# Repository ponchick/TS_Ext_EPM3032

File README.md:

# TS_Ext_EPM3032
EPM3032-based TurboSound extension card for ZXBUS

[CPLD Firmware](https://github.com/MikhaelKaa/Double_ym2149_epm3032)

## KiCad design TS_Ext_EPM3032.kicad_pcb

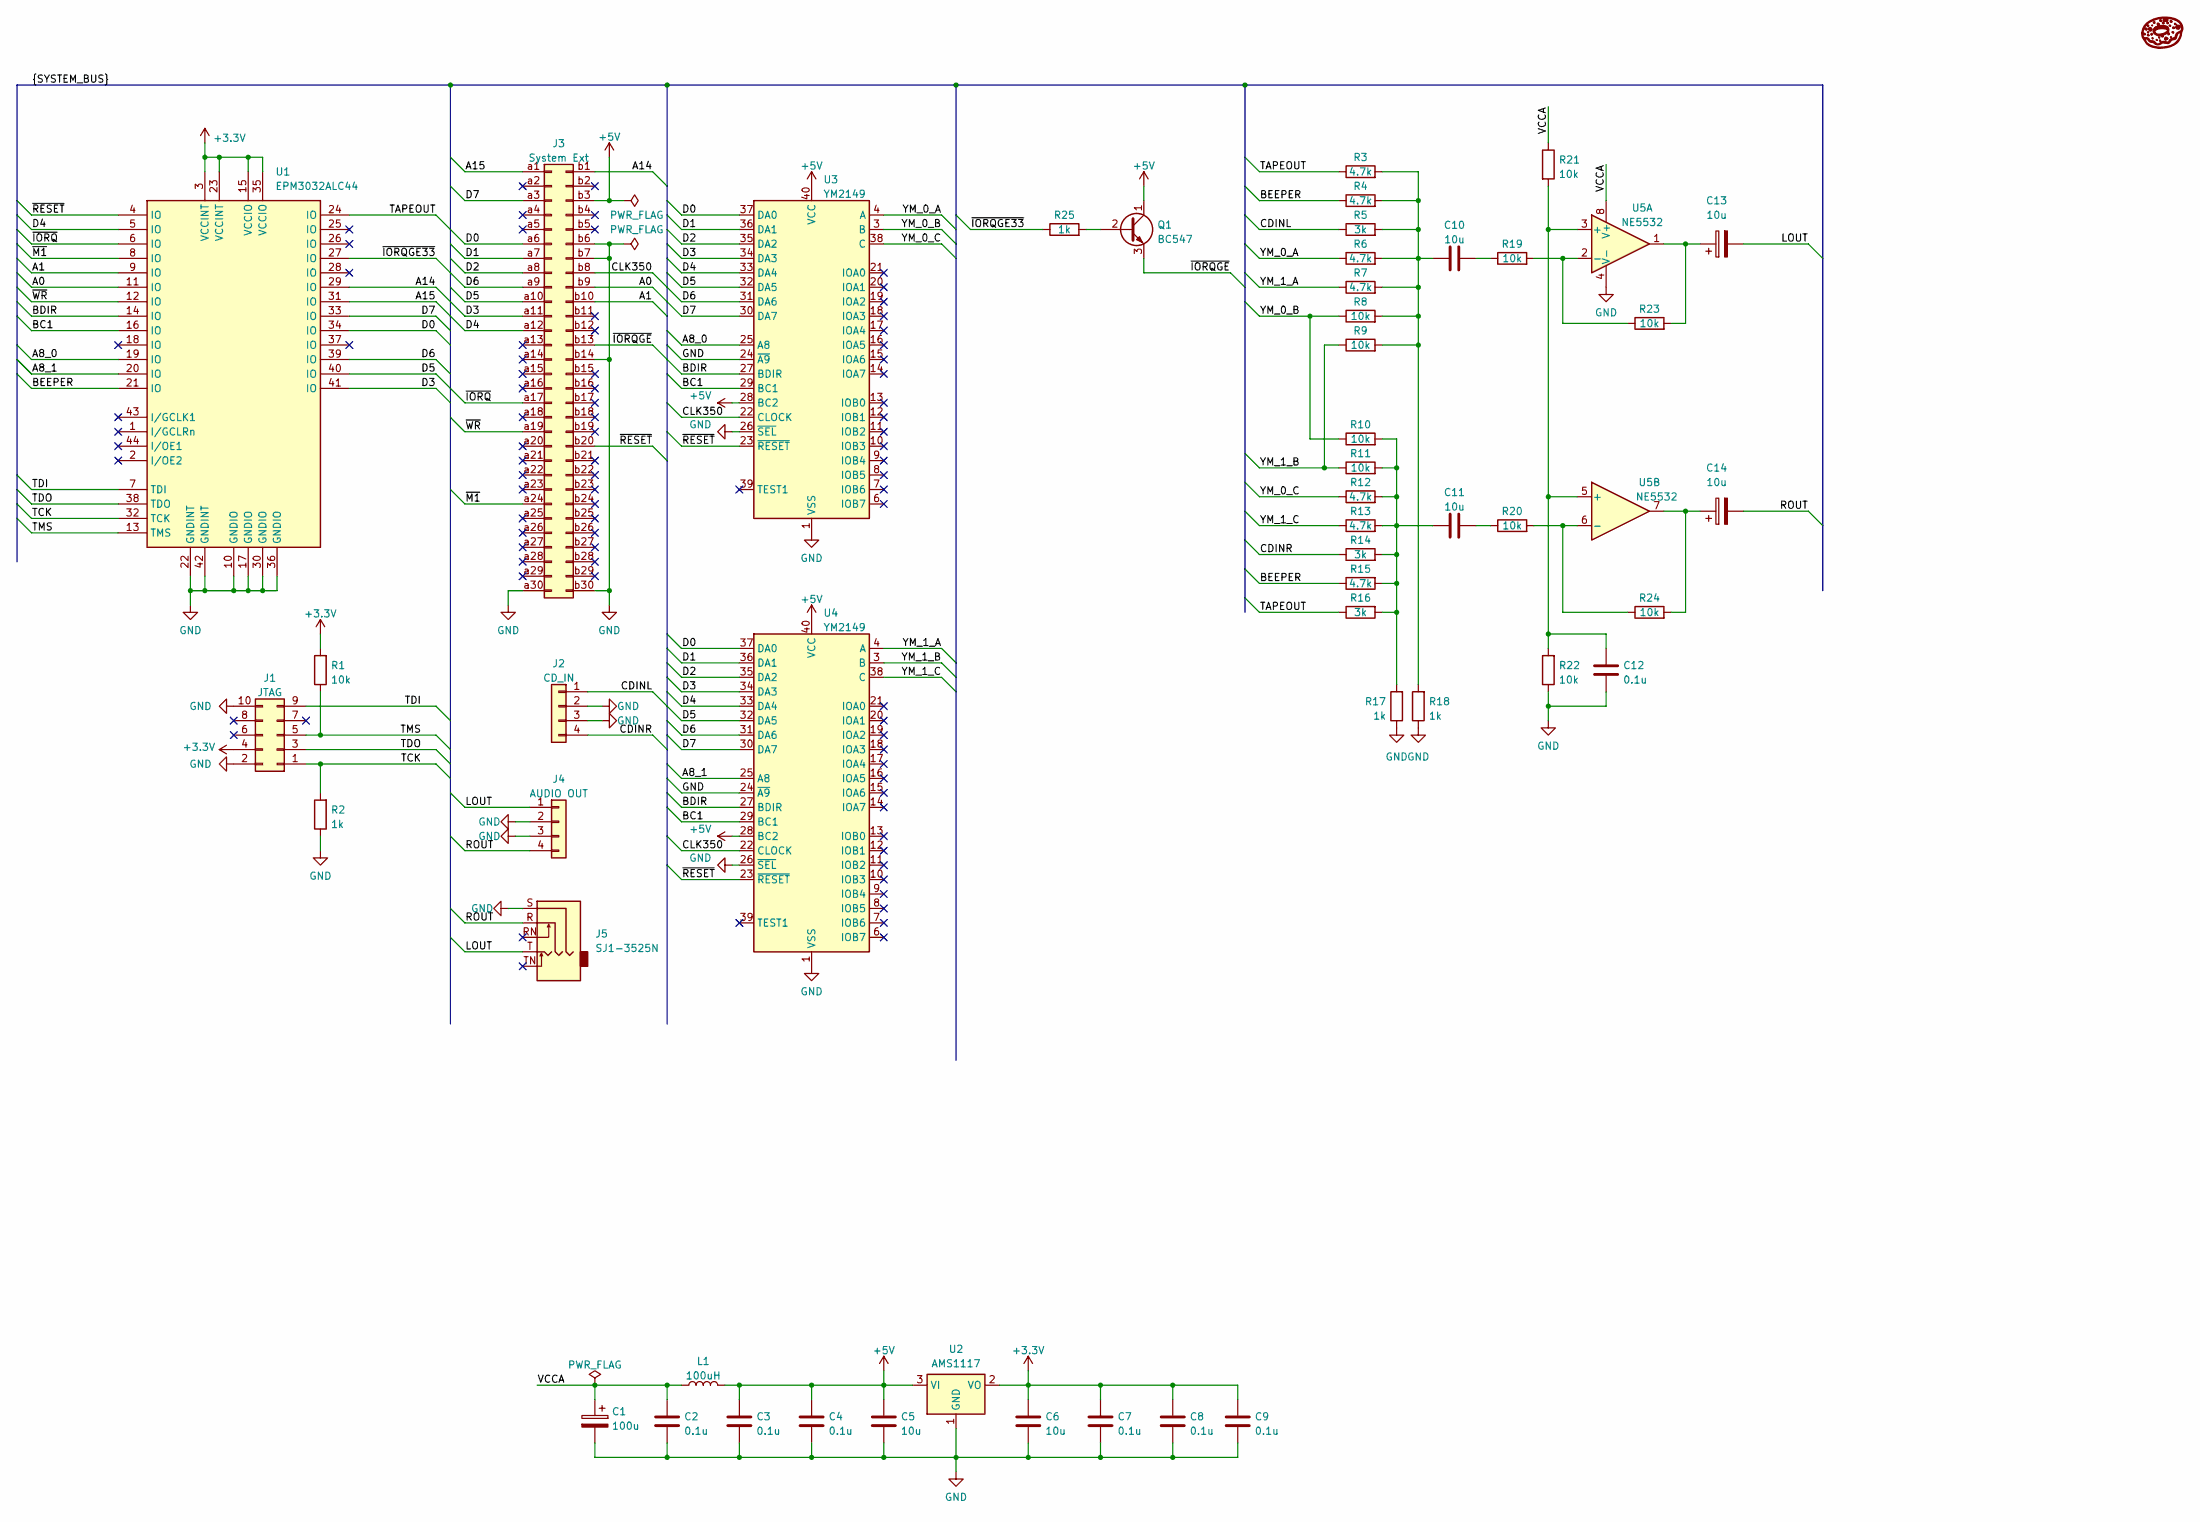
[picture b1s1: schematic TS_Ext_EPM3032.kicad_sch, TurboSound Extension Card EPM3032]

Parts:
C1: 100u; CP_Radial_D5.0mm_P2.50mm
C2, C3, C4, C7, C8, C9, C12: 0.1u; C_Disc_D4.3mm_W1.9mm_P5.00mm
C5, C6: 10u; C_Disc_D4.3mm_W1.9mm_P5.00mm
C10, C11: 10u; C_Rect_L7.0mm_W2.0mm_P5.00mm
C13, C14: 10u; CP_Radial_D5.0mm_P2.50mm
J1: JTAG; IDC-Header_2x05_P2.54mm_Vertical
J2: CD_IN; PinHeader_1x04_P2.54mm_Vertical
J3: System Ext; EDGE SLOT
J4: AUDIO OUT; PinHeader_1x04_P2.54mm_Vertical
J5: SJ1-3525N; Jack_3.5mm_CUI_SJ1-3525N_Horizontal
L1: 100uH; L_Radial_D8.7mm_P5.00mm_Fastron_07HCP
LOGO1: LOGO; ponchick
Q1: BC547; TO-92_Inline
R1, R8, R9, R10, R11, R19, R20, R21, R22, R23, R24: 10k; R_Axial_DIN0204_L3.6mm_D1.6mm_P7.62mm_Horizontal
R2, R17, R18, R25: 1k; R_Axial_DIN0204_L3.6mm_D1.6mm_P7.62mm_Horizontal
R3, R4, R6, R7, R12, R13, R15: 4.7k; R_Axial_DIN0204_L3.6mm_D1.6mm_P7.62mm_Horizontal
R5, R14, R16: 3k; R_Axial_DIN0204_L3.6mm_D1.6mm_P7.62mm_Horizontal
U1: EPM3032ALC44; PLCC-44_THT-Socket
U2: AMS1117; SOT-223-3_TabPin2
U3, U4: YM2149; DIP-40_W15.24mm_Socket
U5: NE5532; DIP-8_W7.62mm_Socket

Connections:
+3.3V: C6.1, C7.1, C8.1, C9.1, J1.4, R1.2, U1.3 (VCCINT), U1.15 (VCCIO), U1.23 (VCCINT), U1.35 (VCCIO), U2.2 (VO)
+5V: C3.1, C4.1, C5.1, J3.b3, L1.2, Q1.1 (C), U2.3 (VI), U3.28 (BC2), U3.40 (VCC), U4.28 (BC2), U4.40 (VCC)
/A0: J3.b9, U1.11 (IO)
/A1: J3.b10, U1.9 (IO)
/A8_0: U1.19 (IO), U3.25 (A8)
/A8_1: U1.20 (IO), U4.25 (A8)
/A14: J3.b1, U1.29 (IO)
/A15: J3.a1, U1.31 (IO)
/BC1: U1.16 (IO), U3.29 (BC1), U4.29 (BC1)
/BDIR: U1.14 (IO), U3.27 (BDIR), U4.27 (BDIR)
/BEEPER: R4.1, R15.1, U1.21 (IO)
/CDINL: J2.1, R5.1
/CDINR: J2.4, R14.1
/CLK350: J3.b8, U3.22 (CLOCK), U4.22 (CLOCK)
/D0: J3.a6, U1.34 (IO), U3.37 (DA0), U4.37 (DA0)
/D1: J3.a7, U3.36 (DA1), U4.36 (DA1)
/D2: J3.a8, U3.35 (DA2), U4.35 (DA2)
/D3: J3.a11, U1.41 (IO), U3.34 (DA3), U4.34 (DA3)
/D4: J3.a12, U1.5 (IO), U3.33 (DA4), U4.33 (DA4)
/D5: J3.a10, U1.40 (IO), U3.32 (DA5), U4.32 (DA5)
/D6: J3.a9, U1.39 (IO), U3.31 (DA6), U4.31 (DA6)
/D7: J3.a3, U1.33 (IO), U3.30 (DA7), U4.30 (DA7)
/LOUT: C13.2, J4.1, J5.T
/ROUT: C14.2, J4.4, J5.R
/TAPEOUT: R3.1, R16.1, U1.24 (IO)
/TCK: J1.1, R2.2, U1.32 (TCK)
/TDI: J1.9, U1.7 (TDI)
/TDO: J1.3, U1.38 (TDO)
/TMS: J1.5, R1.1, U1.13 (TMS)
/VCCA: C1.1, C2.1, L1.1, R21.1, U5.8 (V+)
/YM_0_A: R6.1, U3.4 (A)
/YM_0_B: R8.1, R10.1, U3.3 (B)
/YM_0_C: R12.1, U3.38 (C)
/YM_1_A: R7.1, U4.4 (A)
/YM_1_B: R9.1, R11.1, U4.3 (B)
/YM_1_C: R13.1, U4.38 (C)
/~IORQGE33: R25.1, U1.27 (IO)
/~IORQGE: J3.b13, Q1.3 (E)
/~IORQ: J3.a17, U1.6 (IO)
/~M1: J3.a24, U1.8 (IO)
/~RESET: J3.b20, U1.4 (IO), U3.23 (~RESET), U4.23 (~RESET)
/~WR: J3.a19, U1.12 (IO)
GND: C1.2, C2.2, C3.2, C4.2, C5.2, C6.2, C7.2, C8.2, C9.2, C12.2, J1.2, J1.10, J2.2, J2.3, J3.a30, J3.b6, J3.b7, J3.b14, J3.b30, J4.2, J4.3, J5.S, R2.1, R17.1, R18.1, R22.1, U1.10 (GNDIO), U1.17 (GNDIO), U1.22 (GNDINT), U1.30 (GNDIO), U1.36 (GNDIO), U1.42 (GNDINT), U2.1 (GND), U3.1 (VSS), U3.24 (~A9), U3.26 (~SEL), U4.1 (VSS), U4.24 (~A9), U4.26 (~SEL), U5.4 (V-)
unnamed: C10.1, R3.2, R4.2, R5.2, R6.2, R7.2, R8.2, R9.2, R18.2
unnamed: C10.2, R19.1
unnamed: C11.1, R20.1
unnamed: C11.2, R10.2, R11.2, R12.2, R13.2, R14.2, R15.2, R16.2, R17.2
unnamed: C13.1, R23.2, U5.1
unnamed: C14.1, R24.2, U5.7
unnamed: Q1.2 (B), R25.2
unnamed: C12.1, R21.2, R22.2, U5.3 (+), U5.5 (+)
unnamed: R19.2, R23.1, U5.2 (-)
unnamed: R20.2, R24.1, U5.6 (-)

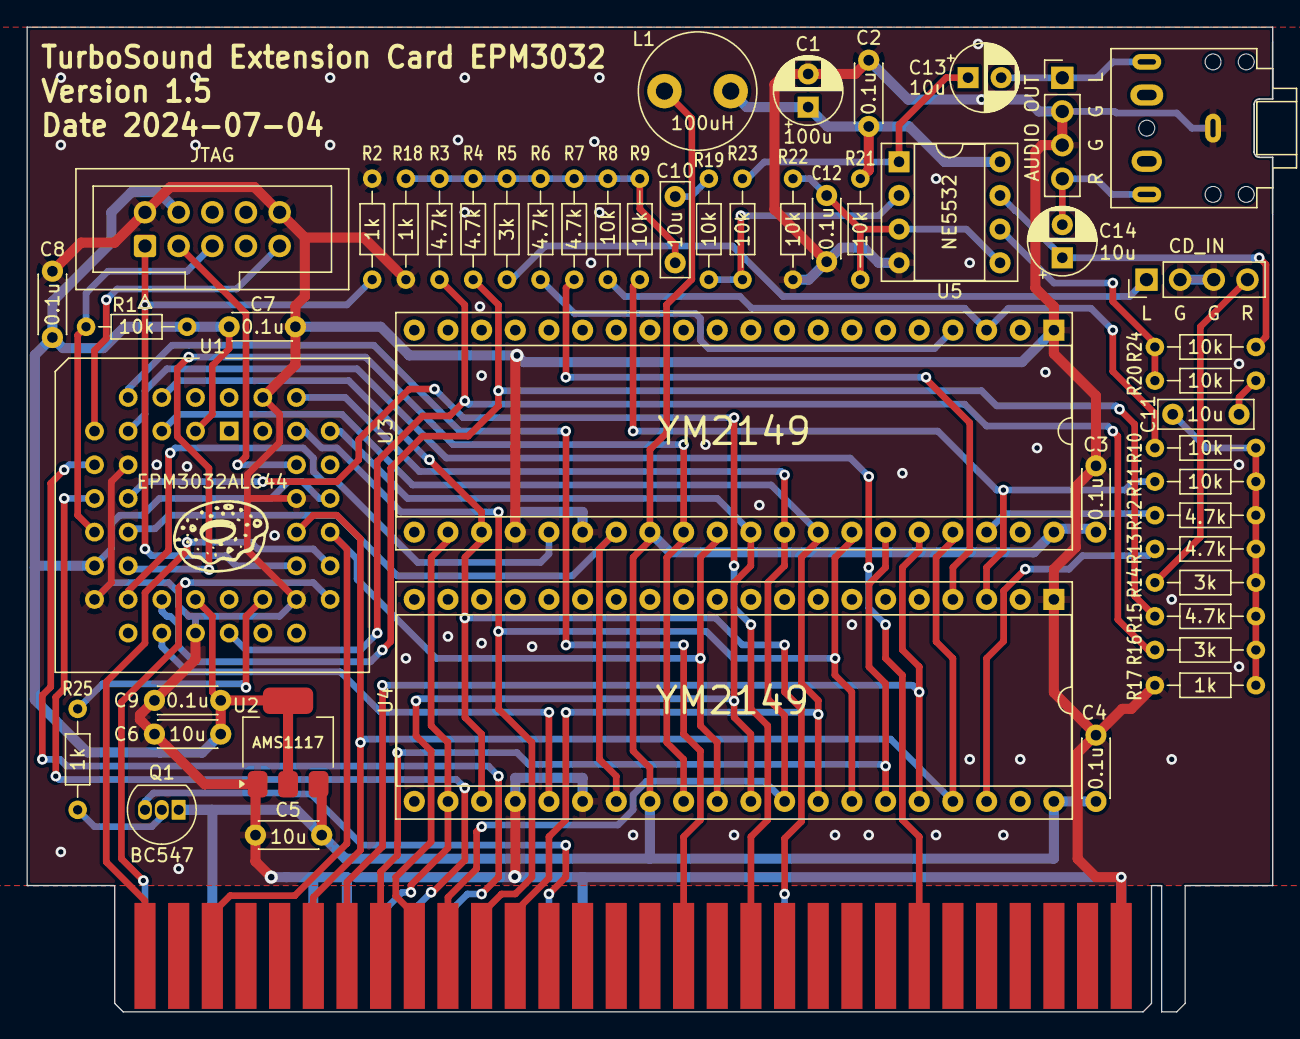
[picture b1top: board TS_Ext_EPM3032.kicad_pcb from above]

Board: 2 copper layers, 94.0 x 74.3 mm, 52 parts (0 on the bottom side), 53 nets.

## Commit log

2022-10-21 Initial commit v0.9
2022-10-21 * Bump to version 1.0 * BOM added * Schematic and gerbers added
2022-10-21 * Bump to version 1.0 * BOM, schematics and gerbers added
2022-10-21 Add missing files
2022-10-26 Remove transistors, reorganize folders
2022-11-05 Fix YM2149F symbol
2022-11-05 Add production files
2023-01-30 Fix pull-up on JTAG connector
2023-01-30 Update gerbers and schematic
2023-01-30 Update gerbers and schematic files
2024-04-10 Remove unused 3d model
2024-04-10 v1.4 production files added
2024-04-10 Migrated to KiCad 8, CPLD value fix
2024-04-10 CPLD FW link added
2024-04-10 ibom config fix path
2024-07-04 Change C13/C14 to electrolytic
